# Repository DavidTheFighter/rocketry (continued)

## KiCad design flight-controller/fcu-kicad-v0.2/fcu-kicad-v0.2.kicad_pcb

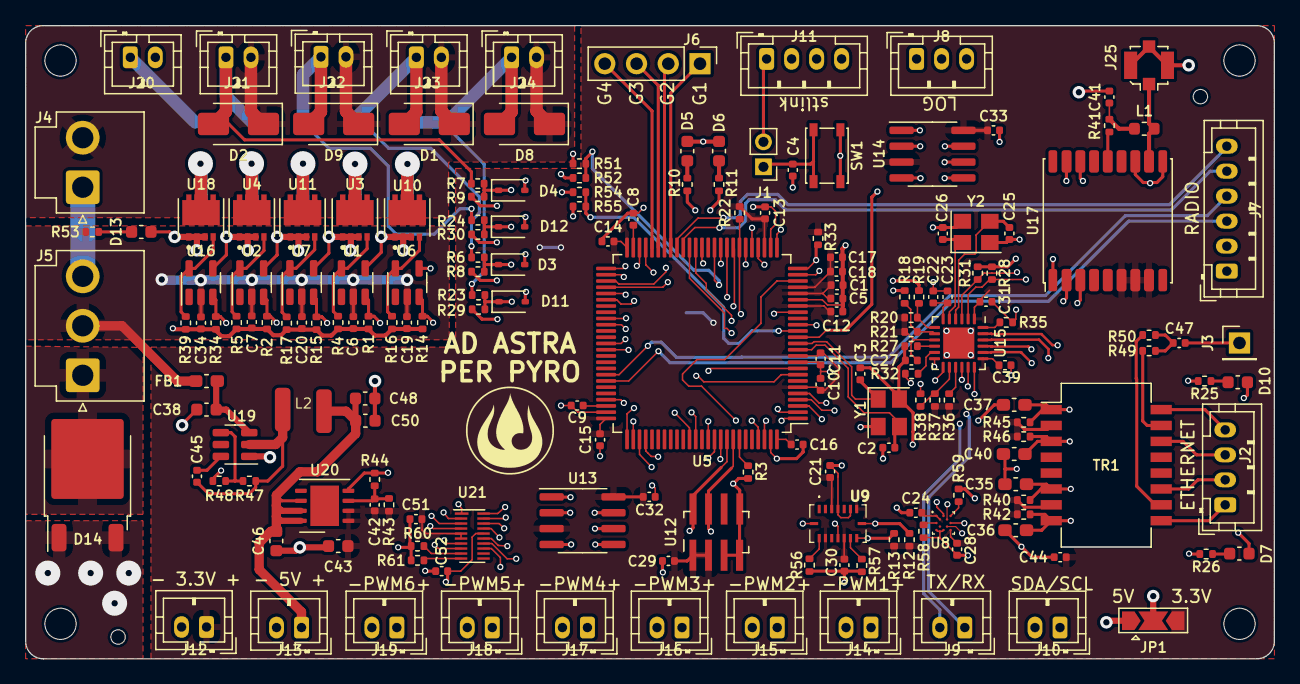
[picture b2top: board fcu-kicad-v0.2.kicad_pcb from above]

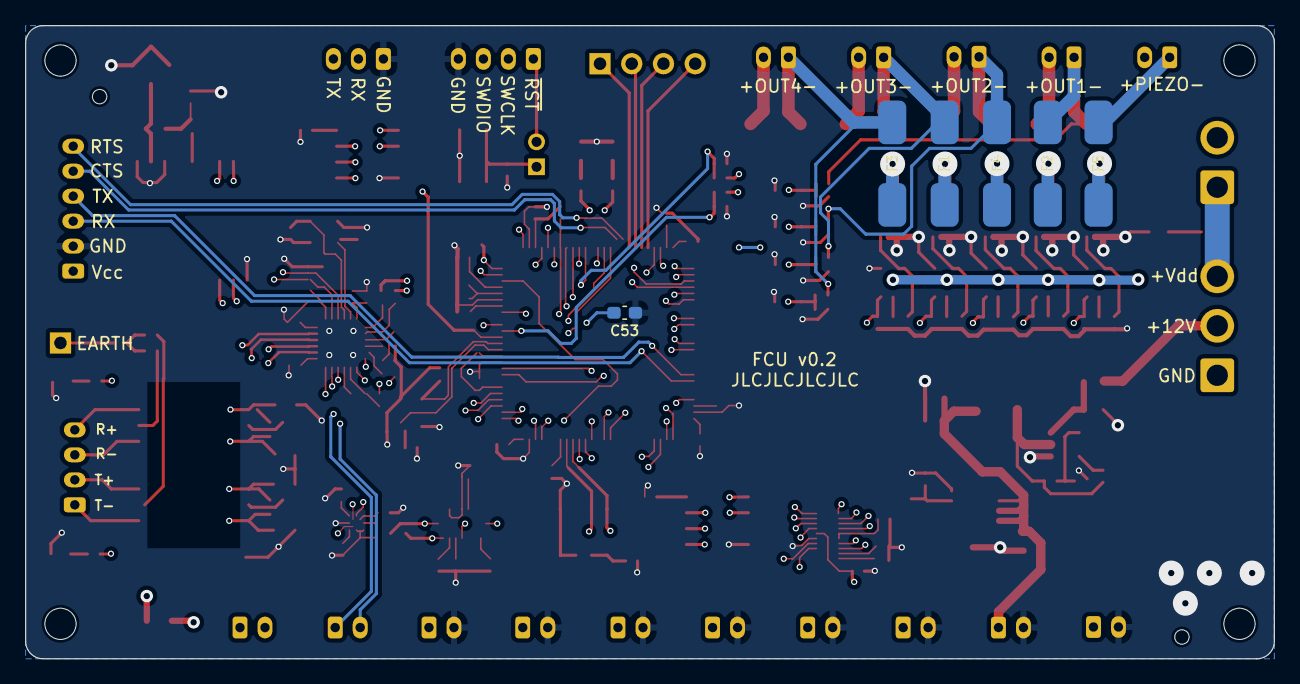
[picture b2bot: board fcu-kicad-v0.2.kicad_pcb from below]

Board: 4 copper layers, 99.9 x 50.7 mm, 186 parts (6 on the bottom side), 138 nets.

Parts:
C1, C6, C7, C17, C19, C20, C22, C34: 1uF; C_0402_1005Metric
C2, C3: 13pF; C_0402_1005Metric
C4, C5, C10, C11, C12, C13, C14, C15, C16, C18, C21, C24, C28, C29, C30, C32, C33, C45, C51, C52: 100nF; C_0402_1005Metric
C8, C9: 2.2uF; C_0402_1005Metric
C23: 470pF; C_0402_1005Metric
C25, C26: 15pF; C_0402_1005Metric
C27, C31, C39, C41: 10nF; C_0402_1005Metric
C35, C36, C37, C40: 10pF; C_0603_1608Metric_Pad1.08x0.95mm_HandSolder
C38, C43, C46: 10uF; C_0603_1608Metric
C42: 470nF; C_0402_1005Metric
C44: 22nF; C_0402_1005Metric
C47: 1nF; C_0402_1005Metric
C48, C50: 22uF; C_0603_1608Metric
C53: 4.7uF; C_0603_1608Metric_Pad1.08x0.95mm_HandSolder
D1, D2, D8, D9: GS1G; D_SMA
D3, D4, D11, D12: MM3Z3V0; D_SOD-323
D5: Blue; C_0603_1608Metric
D6: Red; C_0603_1608Metric
D7: Green; C_0603_1608Metric
D10: Yellow; C_0603_1608Metric
D13: Green_LED; C_0603_1608Metric
D14: MBRD20100; TO-252-2
F1, F2, F3, F4, F5: SF-2410F-T
FB1: FerriteBead; C_0603_1608Metric_Pad1.08x0.95mm_HandSolder
J1: Conn_01x02; PinHeader_1x02_P2.00mm_Vertical
J2, J11: Conn_01x04_Socket; JST_PH_B4B-PH-K_1x04_P2.00mm_Vertical
J3: Conn_01x01; PinHeader_1x01_P2.54mm_Vertical
J4: Conn_01x02_Socket; JST_VH_B2P-VH_1x02_P3.96mm_Vertical
J5: Conn_01x03_Pin; JST_VH_B3P-VH_1x03_P3.96mm_Vertical
J6: Conn_01x04_Socket; PinHeader_1x04_P2.54mm_Vertical
J7: Conn_01x06_Socket; JST_PH_B6B-PH-K_1x06_P2.00mm_Vertical
J8: Conn_01x03_Socket; JST_PH_B3B-PH-K_1x03_P2.00mm_Vertical
J9, J10, J12, J13, J14, J15, J16, J17, J18, J19, J20, J21, J22, J23, J24: Conn_01x02_Socket; JST_PH_B2B-PH-K_1x02_P2.00mm_Vertical
J25: Conn_01x02; U.FL_Molex_MCRF_73412-0110_Vertical
JP1: SolderJumper_3_Open; SolderJumper-3_P2.0mm_Open_TrianglePad1.0x1.5mm
L1: 27nH; L_0603_1608Metric
L2: 3.3uH; CKST353220
R1, R2, R4, R5, R14, R15, R16, R17, R34, R39, R54: 20K; R_0402_1005Metric
R3, R12, R13, R20, R21, R22, R27, R28, R31, R36, R37, R44, R48, R52, R56, R57, R58, R59, R60, R61: 10K; R_0402_1005Metric
R6, R7, R23, R24: 15K; R_0402_1005Metric
R8, R9, R29, R30, R53: 2.4K; R_0402_1005Metric
R10, R11, R25, R26: 220; R_0402_1005Metric
R18, R19, R32, R38: 33; R_0402_1005Metric
R33, R51, R55: 1.5K; R_0402_1005Metric
R35: 12.1K; R_0402_1005Metric
R40, R42, R45, R46: 49.9; R_0402_1005Metric
R41: 10; R_0402_1005Metric
R43, R47: 56.2K; R_0402_1005Metric
R49, R50: 75; R_0402_1005Metric
SW1: SW_RST; SW_SPST_PTS810
TR1: PT61017PEL; Transformer_Ethernet_Bourns_PT61017PEL
U1, U2, U6, U7, U16: MCP1416; SOT-23-5
U3, U4, U10, U11, U18: RQ3E100; HSMT-8
U5: STM32F407VGTx; LQFP-100_14x14mm_P0.5mm
U8: BMM150; WLCSP-12_1.56x1.56mm_P0.4mm
U9: BMI088
U12: MS5611-01BA; LGA-8_3x5mm_P1.25mm_HandSolder
U13, U14: W25X05; SOIC-8_3.9x4.9mm_P1.27mm
U15: LAN8742; VQFN-24-1EP_4x4mm_P0.5mm_EP2.5x2.5mm
U17: MAX-8C; ublox_MAX
U19: AP62300TWU; TSOT-23-6
U20: LD39200; DFN-8-1EP_4x4mm_P0.8mm_EP2.3x3.24mm
U21: TXB0108DQSR; USON-20_2x4mm_P0.4mm
Y1, Y2: 25 MHz; Crystal_SMD_3225-4Pin_3.2x2.5mm

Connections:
+3.3V: C1.1, C5.1, C10.2, C11.2, C12.2, C13.2, C14.2, C15.2, C16.2, C17.2, C18.2, C21.1, C24.2, C27.2, C28.1, C29.1, C30.1, C31.1, C32.2, C33.2, C39.1, C42.2, C43.2, C44.1, C51.2, C53.2, J12.1, JP1.3 (B), R12.2, R13.2, R20.2, R21.2, R22.2, R33.1, R36.2, R37.2, R40.1, R42.1, R43.1, R45.1, R46.1, TR1.2 (C_TD), TR1.7 (C_RD), U5.6 (VBAT), U5.11 (VDD), U5.19 (VDD), U5.21 (VREF+), U5.22 (VDDA), U5.28 (VDD), U5.50 (VDD), U5.75 (VDD), U5.100 (VDD), U8.A1 (PS), U8.B2 (VDDIO), U8.E5 (VDD), U9.3 (VDD), U9.7 (PS), U9.11 (VDDIO), U9.14 (CSB1), U12.1 (VDD), U12.2 (PS), U13.3 (WP), U13.8 (VCC), U14.3 (WP), U14.8 (VCC), U15.1 (VDD2A), U15.9 (VDDIO), U15.19 (VDD1A), U17.6 (V_BCKP), U17.7 (VCC_IO), U17.8 (VCC), U20.1 (OUT), U20.2 (OUT), U21.5 (VCCA), U21.6 (OE)
+5V: C46.2, C48.1, C50.1, C52.2, J13.1, JP1.1 (A), L2.2, U20.6 (EN), U20.7 (IN), U20.8 (IN), U21.16 (VCCB)
+12V: C6.2, C7.2, C19.2, C20.2, C34.2, FB1.1, J5.2, J20.2, R52.1, R53.2, U1.2 (Vdd), U2.2 (Vdd), U6.2 (Vdd), U7.2 (Vdd), U16.2 (Vdd)
/DRX+: C40.1, R46.2, TR1.3 (TD-), U15.23 (RXP)
/DRX-: C37.1, R45.2, TR1.1 (TD+), U15.22 (RXN)
/DTX+: C36.1, R42.2, TR1.8 (RD-), U15.21 (TXP)
/DTX-: C35.1, R40.2, TR1.6 (RD+), U15.20 (TXN)
/RX+: J2.4, TR1.16 (TX+)
/RX-: J2.3, TR1.14 (TX-)
/TX+: J2.2, TR1.11 (RX+)
/TX-: J2.1, TR1.9 (RX-)
ACCEL_INT: U5.39 (PE8), U9.16 (INT1)
ADC1_IN3: D4.1 (K), R7.2, R9.1, U5.26 (PA3)
ADC1_IN4: D12.1 (K), R24.2, R30.1, U5.29 (PA4)
ADC1_IN6: D3.1 (K), R6.2, R8.1, U5.31 (PA6)
ADC1_IN8: D11.1 (K), R23.2, R29.1, U5.35 (PB0)
ADC1_IN9: R51.1, R52.2, U5.36 (PB1)
ADC1_IN10: R54.2, R55.1, U5.15 (PC0)
BLDR_FLASH_CSN: U5.5 (PE6), U14.1 (CS)
BLDR_FLASH_HOLD: U5.38 (PE7), U14.7 (HOLD)
BMM150_INT: U5.18 (PC3), U8.D4 (DRDY)
ETH_CRS_DV: R22.1, R32.1, U5.32 (PA7)
ETH_MDC: U5.16 (PC1), U15.13 (MDC)
ETH_MDIO: R33.2, U5.25 (PA2), U15.12 (MDIO)
ETH_REF_CLK: R38.2, U5.24 (PA1)
ETH_RXD0: R18.2, U5.33 (PC4)
ETH_RXD1: R19.1, U5.34 (PC5)
ETH_TXD0: U5.51 (PB12), U15.17 (TDX0)
ETH_TXD1: U5.52 (PB13), U15.18 (TXD1)
ETH_TX_EN: U5.48 (PB11), U15.16 (TXEN)
Earth: C47.2, J3.1
GND: C1.2, C2.1, C3.1, C4.2, C5.2, C6.1, C7.1, C8.1, C9.1, C10.1, C11.1, C12.1, C13.1, C14.1, C15.1, C16.1, C17.1, C18.1, C19.1, C20.1, C21.2, C22.1, C23.1, C24.1, C25.1, C26.1, C27.1, C28.2, C29.2, C30.2, C31.2, C32.1, C33.1, C34.1, C35.2, C36.2, C37.2, C38.1, C39.2, C40.2, C41.2, C43.1, C44.2, C46.1, C48.2, C50.2, C51.1, C52.1, C53.1, D3.2 (A), D4.2 (A), D5.1 (K), D6.1 (K), D7.1 (K), D10.1 (K), D11.2 (A), D12.2 (A), D13.1 (K), D14.2 (A), J7.2, J8.1, J11.4, J12.2, J13.2, J14.2, J15.2, J16.2, J17.2, J18.2, J19.2, J25.2, R1.1, R2.1, R3.1, R4.2, R5.2, R8.2, R9.2, R14.1, R15.1, R16.2, R17.2, R27.1, R28.2, R29.2, R30.2, R31.2, R34.1, R35.2, R39.2, R44.2, R48.2, R51.2, R55.2, R56.2, R57.2, R58.1, R59.1, R60.2, R61.1, SW1.2 (B), U1.4 (GND), U2.4 (GND), U3.1 (Source), U3.2 (Source), U3.3 (Source), U4.1 (Source), U4.2 (Source), U4.3 (Source), U5.10 (VSS), U5.20 (VSSA), U5.27 (VSS), U5.74 (VSS), U5.99 (VSS), U6.4 (GND), U7.4 (GND), U8.C5 (GND), U8.E1 (GND), U8.E3 (GND), U9.4 (GNDA), U9.6 (GNDIO), U10.1 (Source), U10.2 (Source), U10.3 (Source), U11.1 (Source), U11.2 (Source), U11.3 (Source), U12.3 (GND), U12.4 (CSB), U12.5 (CSB), U13.4 (GND), U14.4 (GND), U15.25 (VSS), U16.4 (GND), U17.1 (GND), U17.10 (GND), U17.12 (GND), U18.1 (Source), U18.2 (Source), U18.3 (Source), U19.1 (GND), U20.4 (GND), U21.15 (GND), Y1.2, Y1.4, Y2.2, Y2.4
GPIO1: J6.1, U5.43 (PE12)
GPIO2: J6.2, U5.44 (PE13)
GPIO3: J6.3, U5.45 (PE14)
GPIO4: J6.4, U5.46 (PE15)
GYRO_INT: U5.40 (PE9), U9.12 (INT3)
I2C1_SCL: J10.1, R12.1, U5.92 (PB6), U8.A3 (SCK), U9.8 (SCL/SCK), U12.8 (SCLK), U17.17 (SCL)
I2C1_SDA: J10.2, R13.1, U5.93 (PB7), U8.B4 (SDI), U9.9 (SDA/SDI), U12.7 (SDI/SDA), U17.16 (SDA)
LOG_FLASH_CSN: U5.3 (PE4), U13.1 (CS)
LOG_FLASH_HOLD: U5.4 (PE5), U13.7 (HOLD)
unnamed: C41.1, L1.1, R41.2
unnamed: C47.1, R49.2, R50.2
unnamed: D5.2 (A), R10.1
unnamed: D6.2 (A), R11.1
unnamed: D7.2 (A), R26.1
unnamed: D10.2 (A), R25.1
unnamed: D13.2 (A), R53.1
unnamed: D14.1 (K), J5.1
unnamed: F1.1, U3.5 (Drain)
unnamed: F2.1, U4.5 (Drain)
unnamed: F3.1, U10.5 (Drain)
unnamed: F4.1, U11.5 (Drain)
unnamed: F5.1, U18.5 (Drain)
unnamed: C4.1, J1.1, SW1.1 (A)
unnamed: J4.1, J5.3, R54.1
unnamed: J7.1, JP1.2 (C)
unnamed: J14.1, U21.20 (B1)
unnamed: J15.1, U21.19 (B2)
unnamed: J16.1, U21.18 (B3)
unnamed: J17.1, U21.17 (B4)
unnamed: J18.1, U21.14 (B5)
unnamed: J19.1, U21.13 (B6)
unnamed: R50.1, TR1.10 (C_RX)
unnamed: R49.1, TR1.15 (C_TX)
unnamed: R4.1, U1.5 (OUT), U3.4 (Gate)
unnamed: R5.1, U2.5 (OUT), U4.4 (Gate)
unnamed: R3.2, U5.94 (BOOT0)
unnamed: R10.2, U5.8 (PC14)
unnamed: R11.2, U5.9 (PC15)
unnamed: C2.2, U5.12 (PH0), Y1.3
unnamed: C3.2, U5.13 (PH1), Y1.1
unnamed: C8.2, U5.49 (VCAP_1)
unnamed: C9.2, U5.73 (VCAP_2)
unnamed: R59.2, U8.A5 (CSB)
unnamed: R58.2, U8.C1 (SDO)
unnamed: R56.1, U9.15 (SDO1)
unnamed: R57.1, U9.10 (SDO2)
unnamed: R16.1, U6.5 (OUT), U10.4 (Gate)
unnamed: R17.1, U7.5 (OUT), U11.4 (Gate)
unnamed: R32.2, U15.11 (CRS_DV)
unnamed: R26.2, R31.1, U15.3 (LED1)
unnamed: R25.2, R28.1, U15.2 (LED2)
unnamed: R35.1, U15.24 (RBIAS)
unnamed: R18.1, R21.1, U15.8 (RXD0)
unnamed: R19.2, R20.1, U15.7 (RXD1)
unnamed: R27.2, U15.10 (RXER)
unnamed: C22.2, C23.2, U15.6 (VDDCR)
unnamed: C25.2, U15.4 (XTAL2), Y2.3
unnamed: C26.2, U15.5 (XTAl1), Y2.1
unnamed: R37.1, R38.1, U15.14 (~INT)
unnamed: R36.1, U15.15 (~RST)
unnamed: R39.1, U16.5 (OUT), U18.4 (Gate)
unnamed: R41.1, U17.14 (VCC_RF)
unnamed: C45.2, U19.6 (BST)
unnamed: R47.2, R48.1, U19.4 (FB)
unnamed: C38.2, FB1.2, U19.3 (IN)
unnamed: C45.1, L2.1, R47.1, U19.2 (SW)
unnamed: C42.1, R43.2, R44.1, U20.3 (ADJ)
unnamed: R60.1, U21.9 (A7)
unnamed: R61.2, U21.10 (A8)
OUT1: D2.2 (A), F2.2, J21.1, R7.1
OUT1_CTRL: R2.2, U2.3 (IN), U5.97 (PE0)
OUT2: D9.2 (A), F4.2, J22.1, R24.1
OUT2_CTRL: R15.2, U5.98 (PE1), U7.3 (IN)
OUT3: D1.2 (A), F1.2, J23.1, R6.1
OUT3_CTRL: R1.2, U1.3 (IN), U5.1 (PE2)
OUT4: D8.2 (A), F3.2, J24.1, R23.1
OUT4_CTRL: R14.2, U5.2 (PE3), U6.3 (IN)
PIEZO: F5.2, J20.1
RADIO_CTS: J7.5, U5.41 (PE10)
RADIO_RTS: J7.6, U5.42 (PE11)
RF_IN: J25.1, L1.2, U17.11 (RF_IN)
SPI1_MISO: U5.90 (PB4), U13.2 (DO)
SPI1_MOSI: U5.91 (PB5), U13.5 (DI)
SPI1_SCK: U5.30 (PA5), U13.6 (CLK)
SPI2_MISO: U5.53 (PB14), U14.2 (DO)
SPI2_MOSI: U5.54 (PB15), U14.5 (DI)
SPI2_SCK: U5.47 (PB10), U14.6 (CLK)
SWCLK: J11.2, U5.76 (PA14)
SWDIO: J11.3, U5.72 (PA13)
TIM2_CH1: U5.77 (PA15), U21.1 (A1)
TIM2_CH2: U5.89 (PB3), U21.2 (A2)
TIM3_CH1: U5.63 (PC6), U21.3 (A3)
TIM3_CH2: U5.64 (PC7), U21.4 (A4)
TIM4_CH1: U5.59 (PD12), U21.7 (A5)
TIM4_CH2: U5.60 (PD13), U21.8 (A6)
TIM5_CH1: R34.2, U5.23 (PA0), U16.3 (IN)
UART4_RX: U5.79 (PC11), U17.2 (TXD)
UART4_TX: U5.78 (PC10), U17.3 (RXD)
USART1_RX: J7.3, U5.69 (PA10)
USART1_TX: J7.4, U5.68 (PA9)
USART2_RX: J8.2, U5.87 (PD6)
USART2_TX: J8.3, U5.86 (PD5)
USART3_RX: J9.1, U5.56 (PD9)
USART3_TX: J9.2, U5.55 (PD8)
Vdrive: D1.1 (K), D2.1 (K), D8.1 (K), D9.1 (K), J4.2, J21.2, J22.2, J23.2, J24.2
~MCU_RST: J1.2, J11.1, U5.14 (NRST)

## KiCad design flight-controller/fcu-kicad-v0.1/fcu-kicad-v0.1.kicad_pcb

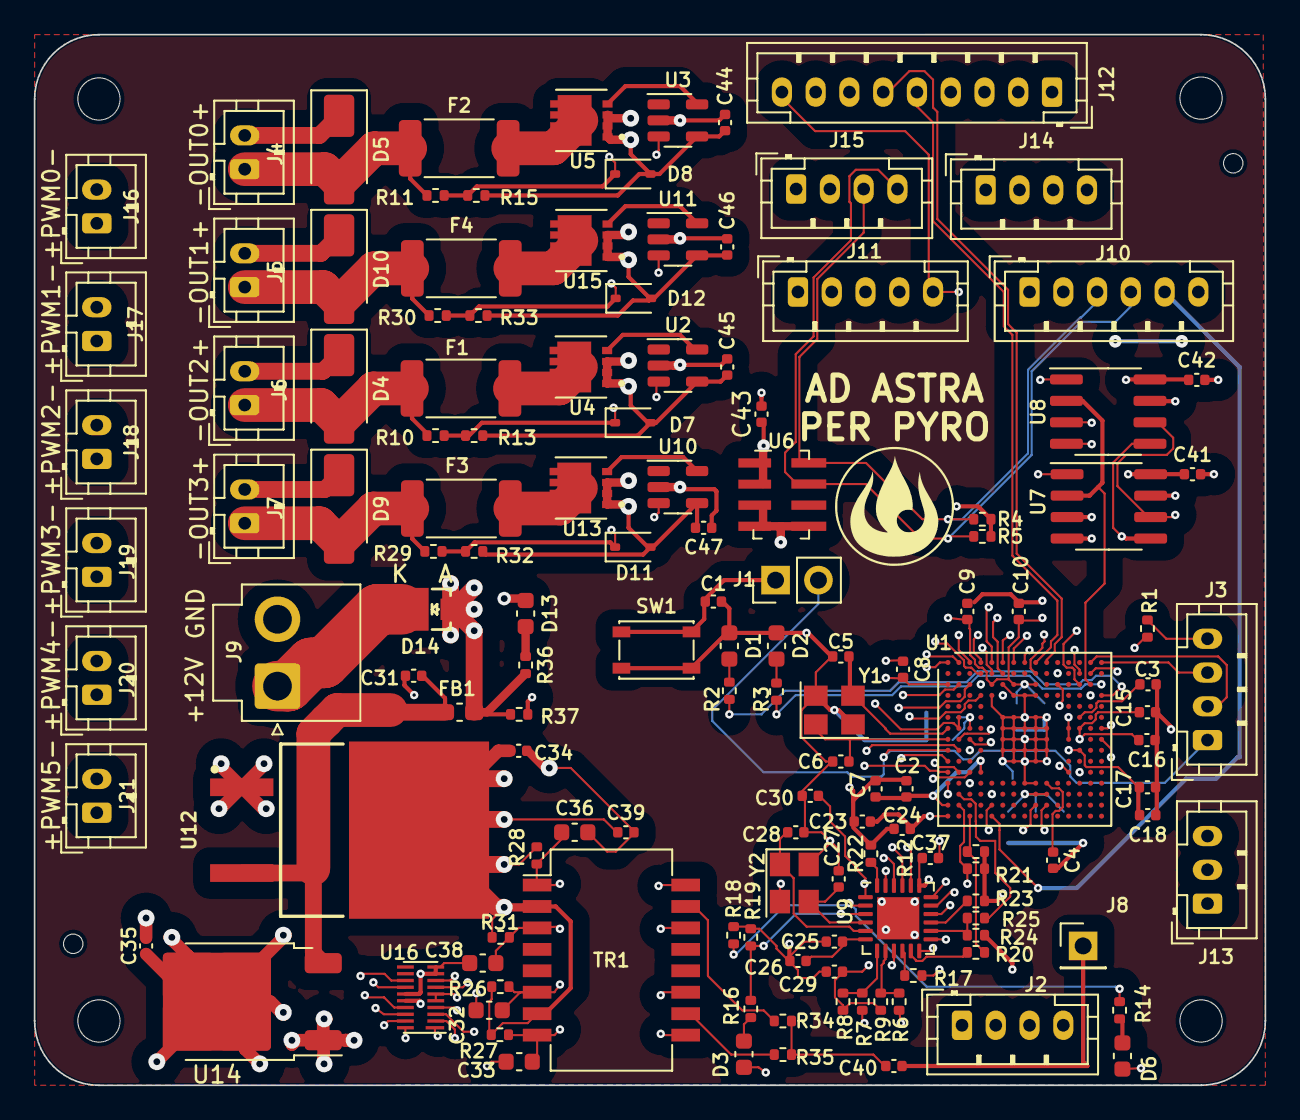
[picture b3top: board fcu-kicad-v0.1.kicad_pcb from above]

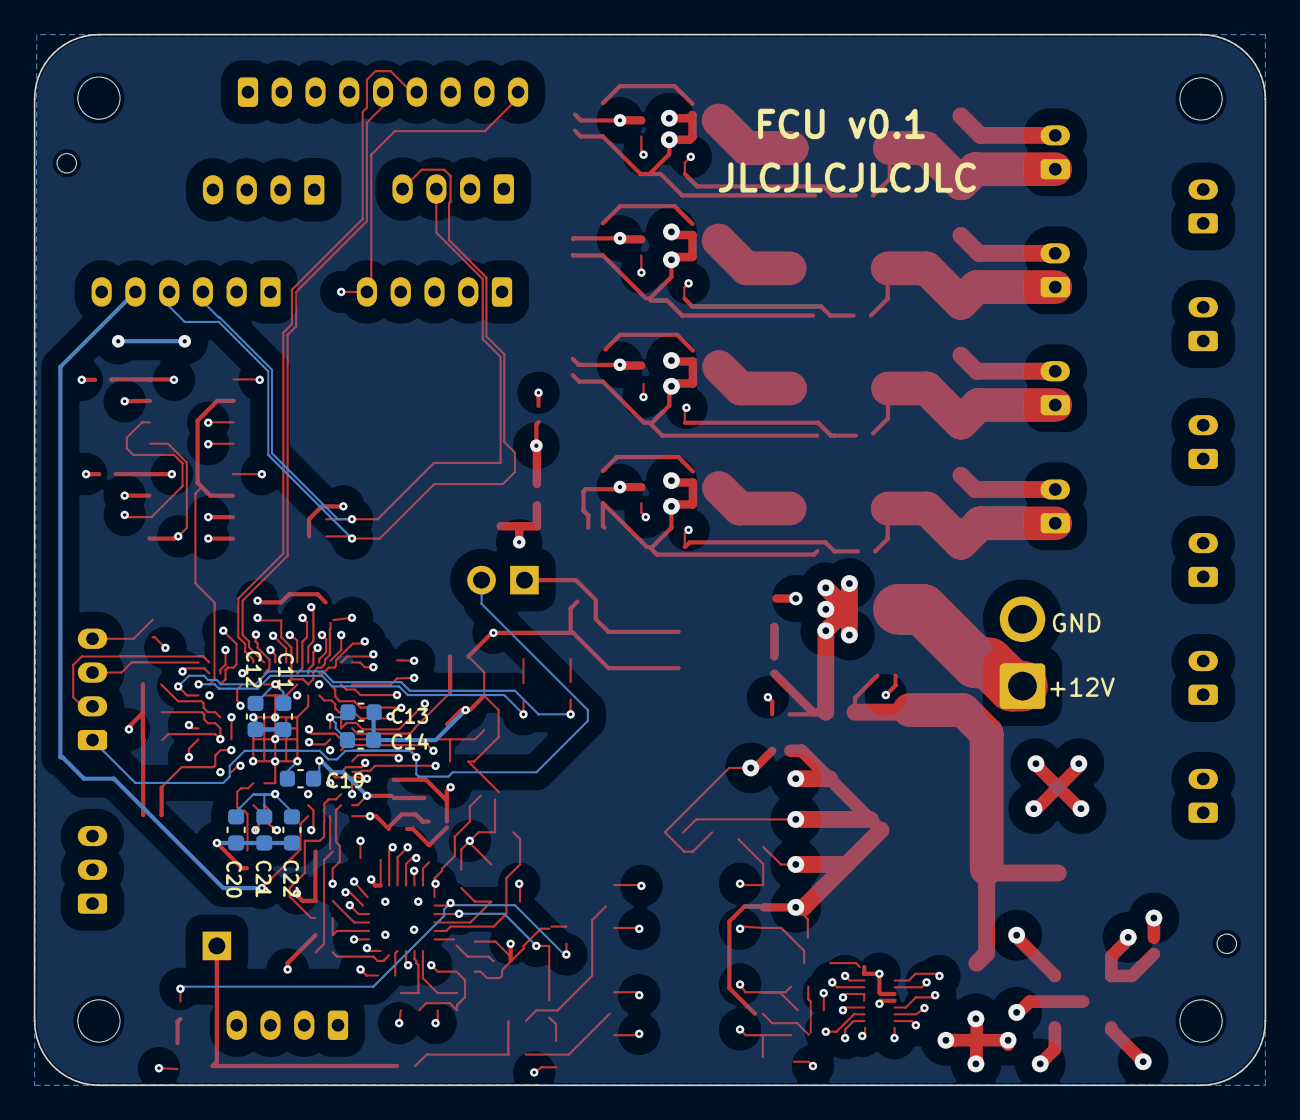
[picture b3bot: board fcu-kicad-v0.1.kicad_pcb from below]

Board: 4 copper layers, 72.9 x 62.2 mm, 144 parts (8 on the bottom side), 110 nets.

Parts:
C1, C7, C8, C9, C10, C15, C16, C17, C18, C24, C41, C42, C43: 100nF; C_0402_1005Metric
C2, C23, C25, C44, C45, C46, C47: 1uF; C_0402_1005Metric
C3, C4: 2.2uF; C_0402_1005Metric
C5, C6: 13pF; C_0402_1005Metric
C11, C12, C13, C14, C19, C20, C21, C22: 100nF; C_0603_1608Metric
C26: 470pF; C_0402_1005Metric
C27, C28: 15pF; C_0402_1005Metric
C29, C30, C37: 10nF; C_0402_1005Metric
C31, C34, C35: 10uF; C_0402_1005Metric
C32, C33, C36, C38: 10pF DNP; C_0603_1608Metric
C39: 22nF; C_0402_1005Metric
C40: 1nF; C_0402_1005Metric
D1: Blue; C_0603_1608Metric
D2: Red; C_0603_1608Metric
D3: Green; C_0603_1608Metric
D4, D5, D9, D10: GS1G; D_SMA
D6: Yellow; C_0603_1608Metric
D7, D8, D11, D12: MM3Z3V0; D_SOD-323
D13: Green_LED; C_0603_1608Metric
D14: SS1P3L-M3/84A; D0-220AA-SMP
F1, F2, F3, F4: SF-2410F-T; Fuse_2512_6332Metric
FB1: FerriteBead; C_0603_1608Metric_Pad1.08x0.95mm_HandSolder
J1: Conn_01x02; PinHeader_1x02_P2.54mm_Vertical
J2, J3, J14, J15: Conn_01x04_Socket; JST_PH_B4B-PH-K_1x04_P2.00mm_Vertical
J4, J5, J6, J7, J16, J17, J18, J19, J20, J21: Conn_01x02_Socket; JST_PH_B2B-PH-K_1x02_P2.00mm_Vertical
J8: Conn_01x01; PinHeader_1x01_P2.54mm_Vertical
J9: Conn_01x02_Pin; JST_VH_B2P-VH_1x02_P3.96mm_Vertical
J10: Conn_01x06_Socket; JST_PH_B6B-PH-K_1x06_P2.00mm_Vertical
J11: Conn_01x05_Socket; JST_PH_B5B-PH-K_1x05_P2.00mm_Vertical
J12: Conn_01x09_Socket; JST_PH_B9B-PH-K_1x09_P2.00mm_Vertical
J13: Conn_01x03_Socket; JST_PH_B3B-PH-K_1x03_P2.00mm_Vertical
R1, R4, R5, R8, R9, R12, R17, R18, R19, R23, R24, R37: 10K; R_0402_1005Metric
R2, R3: 220; R_0402_1005Metric
R6, R7, R20, R25: 33; R_0402_1005Metric
R10, R11, R29, R30: 12K; R_0402_1005Metric
R13, R15, R32, R33: 2.4K; R_0402_1005Metric
R14, R16: 250; R_0402_1005Metric
R21: 1.5K; R_0402_1005Metric
R22: 12.1K; R_0402_1005Metric
R26, R27, R28, R31: 49.9; R_0402_1005Metric
R34, R35: 75; R_0402_1005Metric
R36: 1K; R_0402_1005Metric
SW1: SW_RST; SW_SPST_PTS810
TR1: PT61017PEL; Transformer_Ethernet_Bourns_PT61017PEL
U1: STM32F407IGHx; UFBGA-201_10x10mm_Layout15x15_P0.65mm
U2, U3, U10, U11: MCP1416; SOT-23-5
U4, U5, U13, U15: RQ3E100; HSMT-8
U6: MS5611-01BA; LGA-8_3x5mm_P1.25mm
U7, U8: W25X05; SOIC-8_3.9x4.9mm_P1.27mm
U9: LAN8742; VQFN-24-1EP_4x4mm_P0.5mm_EP2.5x2.5mm
U12: LD1085D2T33R; TO254P1542X460-3N
U14: NCP1117-5.0_SOT223; TO-252-2
U16: TXB0108DQSR; USON-20_2x4mm_P0.4mm
Y1, Y2: 25 MHz; Crystal_SMD_3225-4Pin_3.2x2.5mm

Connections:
+3.3V: C2.1, C7.1, C8.2, C9.2, C10.2, C11.2, C12.2, C13.2, C14.2, C15.2, C16.2, C17.2, C18.2, C19.2, C20.2, C21.2, C22.2, C23.2, C24.2, C29.2, C30.1, C34.1, C37.1, C39.1, C41.1, C42.1, C43.1, J10.1, J11.1, J12.1, J14.1, J15.1, R4.2, R5.2, R8.2, R9.2, R12.2, R21.1, R23.2, R24.2, R26.1, R27.1, R28.1, R31.1, TR1.2 (C_TD), TR1.7 (C_RD), U1.C1 (VBAT), U1.C5 (VDD), U1.C7 (VDD), U1.C8 (VDD), U1.C9 (VDD), U1.F3 (VDD), U1.G3 (VDD), U1.G13 (VDD), U1.H13 (VDD), U1.J12 (VDD), U1.J13 (VDD), U1.K4 (VDD), U1.L4 (BYPASS_REG), U1.N8 (VDD), U1.N9 (VDD), U1.N10 (VDD), U1.P1 (VREF+), U1.R1 (VDDA), U6.1 (VDD), U6.2 (PS), U7.3 (WP), U7.8 (VCC), U8.3 (WP), U8.8 (VCC), U9.1 (VDD2A), U9.9 (VDDIO), U9.19 (VDD1A), U12.4 (VO), U16.5 (VCCA), U16.6 (OE)
+5V: C35.1, U14.2 (VO), U16.16 (VCCB)
+12V: C44.2, C45.2, C46.2, C47.2, D4.1 (K), D5.1 (K), D9.1 (K), D10.1 (K), D14.1 (K), FB1.1, J4.2, J5.2, J6.2, J7.2, R36.2, R37.1, U2.2 (Vdd), U3.2 (Vdd), U10.2 (Vdd), U11.2 (Vdd)
/DRX+: C38.1, R31.2, TR1.3 (TD-), U9.23 (RXP)
/DRX-: C36.1, R28.2, TR1.1 (TD+), U9.22 (RXN)
/DTX+: C33.1, R27.2, TR1.8 (RD-), U9.21 (TXP)
/DTX-: C32.1, R26.2, TR1.6 (RD+), U9.20 (TXN)
/RX+: J2.4, TR1.16 (TX+)
/RX-: J2.3, TR1.14 (TX-)
/TX+: J2.2, TR1.11 (RX+)
/TX-: J2.1, TR1.9 (RX-)
ADC3_IN5: D8.1 (K), R11.2, R15.1, U1.K1 (PF7)
ADC3_IN6: D12.1 (K), R30.2, R33.1, U1.L3 (PF8)
ADC3_IN7: D7.1 (K), R10.2, R13.1, U1.L2 (PF9)
ADC3_IN8: D11.1 (K), R29.2, R32.1, U1.L1 (PF10)
BLDR_FLASH_CSN: U1.C3 (PI6), U8.1 (CS)
BLDR_FLASH_HOLD: U1.C2 (PI7), U8.7 (HOLD)
ETH_CRS_DV: R12.1, R20.1, U1.R3 (PA7)
ETH_MDC: U1.M3 (PC1), U9.13 (MDC)
ETH_MDIO: R21.2, U1.P2 (PA2), U9.12 (MDIO)
ETH_REF_CLK: R25.2, U1.N2 (PA1)
ETH_RXD0: R6.2, U1.N5 (PC4)
ETH_RXD1: R7.1, U1.P5 (PC5)
ETH_TXD0: U1.A8 (PG13), U9.17 (TDX0)
ETH_TXD1: U1.A7 (PG14), U9.18 (TXD1)
ETH_TX_EN: U1.B9 (PG11), U9.16 (TXEN)
Earth: C40.2, J8.1
GND: C1.2, C2.2, C3.1, C4.1, C5.1, C6.1, C7.2, C8.1, C9.1, C10.1, C11.1, C12.1, C13.1, C14.1, C15.1, C16.1, C17.1, C18.1, C19.1, C20.1, C21.1, C22.1, C23.1, C24.1, C25.1, C26.1, C27.1, C28.1, C29.1, C30.2, C31.1, C32.2, C33.2, C34.2, C35.2, C36.2, C37.2, C38.2, C39.2, C41.2, C42.2, C43.2, C44.1, C45.1, C46.1, C47.1, D1.1 (K), D2.1 (K), D3.1 (K), D6.1 (K), D7.2 (A), D8.2 (A), D11.2 (A), D12.2 (A), D13.1 (K), J3.4, J9.2, J10.2, J11.2, J12.2, J13.1, J14.2, J15.2, J16.2, J17.2, J18.2, J19.2, J20.2, J21.2, R1.1, R13.2, R15.2, R17.1, R18.2, R19.2, R22.2, R32.2, R33.2, R37.2, SW1.2 (B), U1.C6 (PDR_ON), U1.D5 (VSS), U1.D7 (VSS), U1.D8 (VSS), U1.D9 (VSS), U1.F2 (VSS), U1.F6 (VSS), U1.F7 (VSS), U1.F8 (VSS), U1.F9 (VSS), U1.F10 (VSS), U1.F12 (VSS), U1.G2 (VSS), U1.G6 (VSS), U1.G7 (VSS), U1.G8 (VSS), U1.G9 (VSS), U1.G10 (VSS), U1.G12 (VSS), U1.H6 (VSS), U1.H7 (VSS), U1.H8 (VSS), U1.H9 (VSS), U1.H10 (VSS), U1.H12 (VSS), U1.J6 (VSS), U1.J7 (VSS), U1.J8 (VSS), U1.J9 (VSS), U1.J10 (VSS), U1.K6 (VSS), U1.K7 (VSS), U1.K8 (VSS), U1.K9 (VSS), U1.K10 (VSS), U1.M1 (VSSA), U1.M8 (VSS), U1.M9 (VSS), U1.N1 (VREF-), U2.4 (GND), U3.4 (GND), U4.1 (Source), U4.2 (Source), U4.3 (Source), U5.1 (Source), U5.2 (Source), U5.3 (Source), U6.3 (GND), U6.4 (CSB), U6.5 (CSB), U7.4 (GND), U8.4 (GND), U9.25 (VSS), U10.4 (GND), U11.4 (GND), U12.1 (GND), U13.1 (Source), U13.2 (Source), U13.3 (Source), U14.1 (GND), U15.1 (Source), U15.2 (Source), U15.3 (Source), U16.9 (A7), U16.10 (A8), U16.15 (GND), Y1.2, Y1.4, Y2.2, Y2.4
I2C1_SCL: J10.3, J15.3, R4.1, U1.A5 (PB8), U6.8 (SCLK)
I2C1_SDA: J10.4, J15.4, R5.1, U1.B4 (PB9), U6.7 (SDI/SDA)
IMU_IRQ: J10.6, U1.A1 (PE3)
LOG_FLASH_CSN: U1.D4 (PI4), U7.1 (CS)
LOG_FLASH_HOLD: U1.C4 (PI5), U7.7 (HOLD)
unnamed: C40.1, R34.2, R35.2
unnamed: D1.2 (A), R2.1
unnamed: D2.2 (A), R3.1
unnamed: D3.2 (A), R16.1
unnamed: D6.2 (A), R14.1
unnamed: D13.2 (A), R36.1
unnamed: D14.2 (A), J9.1
unnamed: F1.1, U4.5 (Drain)
unnamed: F2.1, U5.5 (Drain)
unnamed: F3.1, U13.5 (Drain)
unnamed: F4.1, U15.5 (Drain)
unnamed: C1.1, J1.1, SW1.1 (A)
unnamed: J16.1, U16.20 (B1)
unnamed: J17.1, U16.19 (B2)
unnamed: J18.1, U16.18 (B3)
unnamed: J19.1, U16.17 (B4)
unnamed: J20.1, U16.14 (B5)
unnamed: J21.1, U16.13 (B6)
unnamed: R35.1, TR1.10 (C_RX)
unnamed: R34.1, TR1.15 (C_TX)
unnamed: R1.2, U1.D6 (BOOT0)
unnamed: R2.2, U1.D15 (PA10)
unnamed: R3.2, U1.C15 (PA11)
unnamed: C5.2, U1.G1 (PH0), Y1.3
unnamed: C6.2, U1.H1, Y1.1
unnamed: C4.2, U1.M10 (VCAP_1)
unnamed: C3.2, U1.F13 (VCAP_2)
unnamed: U2.5 (OUT), U4.4 (Gate)
unnamed: U3.5 (OUT), U5.4 (Gate)
unnamed: R20.2, U9.11 (CRS_DV)
unnamed: R16.2, R19.1, U9.3 (LED1)
unnamed: R14.2, R18.1, U9.2 (LED2)
unnamed: R22.1, U9.24 (RBIAS)
unnamed: R6.1, R9.1, U9.8 (RXD0)
unnamed: R7.2, R8.1, U9.7 (RXD1)
unnamed: R17.2, U9.10 (RXER)
unnamed: C25.2, C26.2, U9.6 (VDDCR)
unnamed: C27.2, U9.4 (XTAL2), Y2.3
unnamed: C28.2, U9.5 (XTAl1), Y2.1
unnamed: R24.1, R25.1, U9.14 (~INT)
unnamed: R23.1, U9.15 (~RST)
unnamed: U10.5 (OUT), U13.4 (Gate)
unnamed: U11.5 (OUT), U15.4 (Gate)
unnamed: C31.2, FB1.2, U12.3 (VI), U14.3 (VI)
RADIO_CE: J12.8, U1.A2 (PE2)
RADIO_IRQ: J12.7, U1.A3 (PE1)
SPI1_MISO: J12.5, U1.A9 (PB4)
SPI1_MOSI: J12.4, U1.A6 (PB5)
SPI1_SCK: J12.6, U1.A10 (PB3)
SPI2_MISO: U1.C14 (PI2), U7.2 (DO), U8.2 (DO)
SPI2_MOSI: U1.C13 (PI3), U7.5 (DI), U8.5 (DI)
SPI2_SCK: U1.D14 (PI1), U7.6 (CLK), U8.6 (CLK)
SWCLK: J3.2, U1.A14
SWDIO: J3.3, U1.A15 (PA13)
SWT1: D5.2 (A), F2.2, J4.1, R11.1
SWT1_CTRL: U1.H3 (PF1), U3.3 (IN)
SWT2: D10.2 (A), F4.2, J5.1, R30.1
SWT2_CTRL: U1.H2 (PF2), U11.3 (IN)
SWT3: D4.2 (A), F1.2, J6.1, R10.1
SWT3_CTRL: U1.J2 (PF3), U2.3 (IN)
SWT4: D9.2 (A), F3.2, J7.1, R29.1
SWT4_CTRL: U1.J3 (PF4), U10.3 (IN)
TIM1_CH1: U1.P9 (PE9), U16.1 (A1)
TIM1_CH2: U1.P10 (PE11), U16.2 (A2)
TIM3_CH1: U1.H15 (PC6), U16.3 (A3)
TIM3_CH2: U1.G15 (PC7), U16.4 (A4)
TIM5_CH1: U1.L13 (PH10), U16.7 (A5)
TIM5_CH2: U1.L12 (PH11), U16.8 (A6)
USART1_RX: J11.3, U1.B5 (PB7)
USART1_TX: J11.4, U1.B6
USART2_RX: J13.2, U1.B11 (PD6)
USART2_TX: J13.3, U1.C11 (PD5)
USART3_RX: J14.3, U1.B13 (PC11)
USART3_TX: J14.4, U1.B14 (PC10)
~CSN_RADIO: J12.3, U1.A4 (PE0)
~MCU_RST: J1.2, J3.1, U1.J1 (NRST)
~RST: J10.5, J11.5, J12.9, U1.R5 (PB0)

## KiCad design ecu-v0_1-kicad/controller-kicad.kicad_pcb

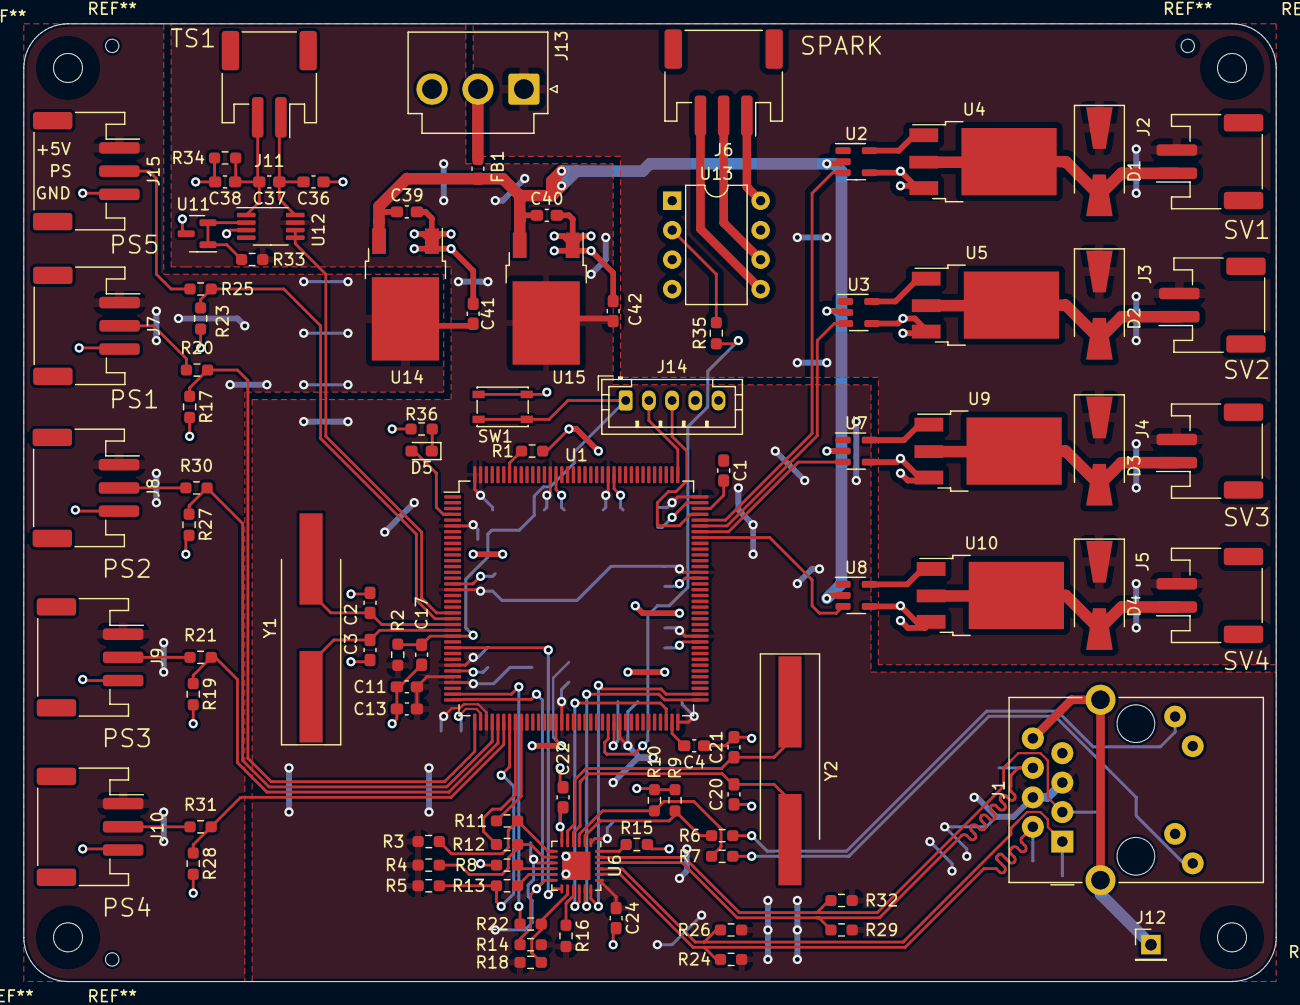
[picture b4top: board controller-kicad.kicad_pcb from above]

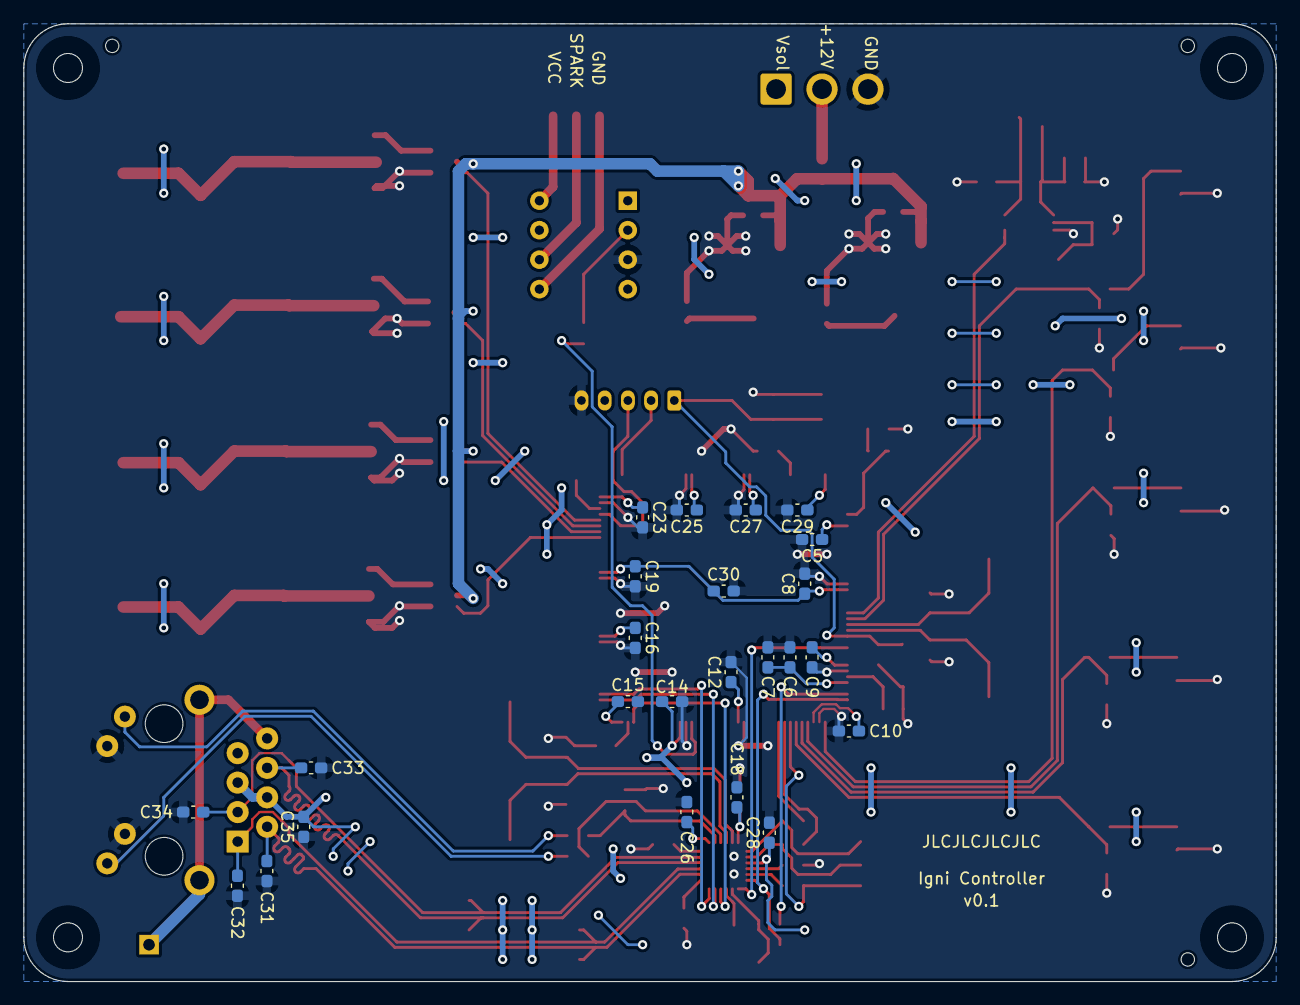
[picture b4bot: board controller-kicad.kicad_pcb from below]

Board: 2 copper layers, 108.0 x 82.5 mm, 117 parts (24 on the bottom side), 75 nets.

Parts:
C1, C4: 2.2uF; C_0603_1608Metric_Pad1.08x0.95mm_HandSolder
C2, C3: 23pF; C_0603_1608Metric_Pad1.08x0.95mm_HandSolder
C5, C6, C8, C9, C10, C11, C12, C14, C15, C16, C17, C19, C23, C25, C27, C29, C37: 100nF; C_0603_1608Metric_Pad1.08x0.95mm_HandSolder
C7, C13, C18: 1uF; C_0603_1608Metric_Pad1.08x0.95mm_HandSolder
C20, C21: 27pF; C_0603_1608Metric_Pad1.08x0.95mm_HandSolder
C22: 470pF; C_0603_1608Metric_Pad1.08x0.95mm_HandSolder
C24, C26, C28, C36, C38: 10nF; C_0603_1608Metric_Pad1.08x0.95mm_HandSolder
C30: 4.7uF; C_0603_1608Metric_Pad1.08x0.95mm_HandSolder
C31, C32, C33, C34: 10pF DNP; C_0603_1608Metric_Pad1.08x0.95mm_HandSolder
C35: 22nF; C_0603_1608Metric_Pad1.08x0.95mm_HandSolder
C39, C40, C41, C42: 10uF; C_0603_1608Metric_Pad1.08x0.95mm_HandSolder
D1, D2, D3, D4: D_Small; D_SMA-SMB_Universal_Handsoldering
D5: LED_Small; LED_0603_1608Metric_Pad1.05x0.95mm_HandSolder
FB1: FerriteBead_Small; C_0603_1608Metric_Pad1.08x0.95mm_HandSolder
J1: RJ45_Amphenol_RJMG1BD3B8K1ANR
J2, J3, J4, J5, J11: Conn_01x02_Female; JST_PH_S2B-PH-SM4-TB_1x02-1MP_P2.00mm_Horizontal
J6, J7, J8, J9, J10, J15: Conn_01x03_Female; JST_PH_S3B-PH-SM4-TB_1x03-1MP_P2.00mm_Horizontal
J12: Conn_01x01; PinHeader_1x01_P2.54mm_Vertical
J13: Conn_01x03_Male; JST_VH_B3P-VH-B_1x03_P3.96mm_Vertical
J14: Conn_01x05_Female; JST_PH_B5B-PH-K_1x05_P2.00mm_Vertical
R1, R2, R3, R4, R5, R8, R9, R10, R16, R18: 10K; R_0603_1608Metric_Pad0.98x0.95mm_HandSolder
R6, R7: 150; R_0603_1608Metric_Pad0.98x0.95mm_HandSolder
R11, R12, R13, R22: 33; R_0603_1608Metric_Pad0.98x0.95mm_HandSolder
R14, R17, R19, R23, R27, R28: 1.5K; R_0603_1608Metric_Pad0.98x0.95mm_HandSolder
R15: 12.1K; R_0603_1608Metric_Pad0.98x0.95mm_HandSolder
R20, R21, R25, R30, R31: 750; R_0603_1608Metric_Pad0.98x0.95mm_HandSolder
R24, R26, R29, R32: 49.9 1%; R_0603_1608Metric_Pad0.98x0.95mm_HandSolder
R33: 1K; R_0603_1608Metric_Pad0.98x0.95mm_HandSolder
R34: 1M; R_0603_1608Metric_Pad0.98x0.95mm_HandSolder
R35: 350; R_0603_1608Metric_Pad0.98x0.95mm_HandSolder
R36: 220; R_0603_1608Metric_Pad0.98x0.95mm_HandSolder
SW1: SW_RST; SW_SPST_PTS810
U1: STM32F407ZETx; LQFP-144_20x20mm_P0.5mm
U2, U3, U7, U8: MCP1416; SOT-23-5
U4, U5, U9, U10: IPD60R600; TO-252-3_TabPin2-HandSolder
U6: LAN8742; VQFN-24-1EP_4x4mm_P0.5mm_EP2.45x2.45mm
U11: TL431DBZ; SOT-23
U12: AD8495; MSOP-8_3x3mm_P0.65mm
U13: TLP250; DIP-8_W7.62mm
U14: NCP1117-5.0_TO252; TO-252-2-HandSolder
U15: NCP1117-3.3_TO252; TO-252-2-HandSolder
Y1, Y2: 25 MHz; Crystal_SMD_HC49-SD_HandSoldering

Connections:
+5V: C41.1, J7.1, J8.1, J9.1, J10.1, J15.1, U14.2 (VO)
+12V: C39.1, C40.1, FB1.1, U2.2 (Vdd), U3.2 (Vdd), U7.2 (Vdd), U8.2 (Vdd), U14.3 (VI), U15.3 (VI)
/RX+: C34.1, J1.R3 (RD+), R32.2, U6.23 (RXP)
/RX-: C33.1, J1.R6 (RD-), R29.2, U6.22 (RXN)
/TX+: C32.1, J1.R1 (TD+), R26.2, U6.21 (TXP)
/TX-: C31.1, J1.R2 (TD-), R24.2, U6.20 (TXN)
ADC1_IN3: R17.1, R20.1, U1.37 (PA3)
ADC1_IN4: R27.1, R30.1, U1.40 (PA4)
ADC2_IN5: R19.1, R21.1, U1.41 (PA5)
ADC2_IN6: R28.1, R31.1, U1.42 (PA6)
ADC3_IN7: U1.21 (PF9), U12.5 (SENSE), U12.6
ADC3_IN8: R23.1, R25.1, U1.22 (PF10)
ETH_CRS_DV: R5.1, R13.1, U1.43 (PA7)
ETH_LED1: J1.L4 (LEDG_A), R7.1
ETH_LED2: J1.L1 (LEDY_A), R6.1
ETH_MDC: U1.27 (PC1), U6.13 (MDC)
ETH_MDIO: R14.2, U1.36 (PA2), U6.12 (MDIO)
ETH_REF_CLK: R22.2, U1.35 (PA1)
ETH_RXD0: R12.2, U1.44 (PC4)
ETH_RXD1: R11.1, U1.45 (PC5)
ETH_TXD0: U1.73 (PB12), U6.17 (TDX0)
ETH_TXD1: U1.74 (PB13), U6.18 (TXD1)
ETH_TX_EN: U1.70 (PB11), U6.16 (TXEN)
Earth: J1.13 (SHIELD), J1.R8 (GND), J12.1
GND: C1.1, C2.1, C3.1, C4.1, C5.2, C6.2, C7.2, C8.2, C9.2, C10.2, C11.2, C12.2, C13.2, C14.2, C15.2, C16.2, C17.2, C18.1, C19.2, C20.1, C21.1, C22.1, C23.2, C24.2, C25.2, C26.2, C27.2, C28.2, C29.2, C30.2, C31.2, C32.2, C33.2, C34.2, C35.1, C36.1, C38.2, C39.2, C40.2, C41.2, C42.2, J1.L2 (LEDY_K), J1.L3 (LEDG_K), J7.3, J8.3, J9.3, J10.3, J13.3, J14.5, J15.3, R1.1, R8.1, R9.2, R10.2, R15.2, R17.2, R19.2, R23.2, R27.2, R28.2, R34.2, R36.2, SW1.2 (B), U1.16 (VSS), U1.31 (VSSA), U1.38 (VSS), U1.51 (VSS), U1.61 (VSS), U1.83 (VSS), U1.94 (VSS), U1.107 (VSS), U1.120 (VSS), U1.130 (VSS), U2.4 (GND), U3.4 (GND), U4.3 (SOURCE), U5.3 (SOURCE), U6.25 (VSS), U7.4 (GND), U8.4 (GND), U9.3 (SOURCE), U10.3 (SOURCE), U11.3 (A), U12.3 (-Vs), U13.3 (C), U14.1 (GND), U15.1 (GND)
unnamed: C1.2, U1.106 (VCAP_2)
unnamed: C2.2, U1.23 (PH0), Y1.2
unnamed: C3.2, U1.24 (PH1), Y1.1
unnamed: C4.2, U1.71 (VCAP_1)
unnamed: C18.2, C22.2, U6.6 (VDDCR)
unnamed: C20.2, U6.4 (XTAL2), Y2.2
unnamed: C21.2, U6.5 (XTAl1), Y2.1
unnamed: D5.1 (K), R36.1
unnamed: D5.2 (A), U1.4 (PE5)
unnamed: FB1.2, J13.2
unnamed: R1.2, U1.138 (BOOT0)
unnamed: R6.2, R9.1, U6.2 (LED2)
unnamed: R8.2, U6.10 (RXER)
unnamed: R7.2, R10.1, U6.3 (LED1)
unnamed: R3.1, R11.2, U6.7 (RXD1)
unnamed: R4.1, R12.1, U6.8 (RXD0)
unnamed: R13.2, U6.11 (CRS_DV)
unnamed: R15.1, U6.24 (RBIAS)
unnamed: R16.1, U6.15 (~RST)
unnamed: R18.1, R22.1, U6.14 (~INT)
unnamed: R33.1, U11.1 (K), U11.2 (REF), U12.2 (REF)
unnamed: R35.2, U13.2 (A)
unnamed: U2.5 (OUT), U4.1 (GATE)
unnamed: U3.5 (OUT), U5.1 (GATE)
unnamed: U7.5 (OUT), U9.1 (GATE)
unnamed: U8.5 (OUT), U10.1 (GATE)
PS1: J7.2, R20.2
PS2: J8.2, R30.2
PS3: J9.2, R21.2
PS4: J10.2, R31.2
PS5: J15.2, R25.2
RST: C17.1, J14.1, R2.2, SW1.1 (A), U1.25 (NRST)
SPARK: J6.2, U13.6 (VO)
SPARK_CTRL: R35.1, U1.60 (PE9)
SPARK_GND: J6.3, U13.5 (VEE)
SPARK_VCC: J6.1, U13.8 (VCC)
SV1: D1.2 (A), J2.1, U4.2 (DRAIN)
SV1_CTRL: U1.104 (PA12), U2.3 (IN)
SV2: D2.2 (A), J3.1, U5.2 (DRAIN)
SV2_CTRL: U1.103 (PA11), U3.3 (IN)
SV3: D3.2 (A), J4.1, U9.2 (DRAIN)
SV3_CTRL: U1.102 (PA10), U7.3 (IN)
SV4: D4.2 (A), J5.1, U10.2 (DRAIN)
SV4_CTRL: U1.101 (PA9), U8.3 (IN)
SWCLK: J14.2, U1.109 (PA14)
SWDIO: J14.3, U1.105 (PA13)
TS1+: C36.2, C37.1, J11.1, U12.8 (+IN)
TS1-: C37.2, C38.1, J11.2, R34.1, U12.1 (-IN)
VBAT: C5.1, C6.1, C7.1, C8.1, C9.1, C10.1, C11.1, C12.1, C13.1, C14.1, C15.1, C16.1, C19.1, C23.1, C24.1, C25.1, C26.1, C27.1, C28.1, C29.1, C30.1, C35.2, C42.1, J1.R4 (TCT), J1.R5 (RCT), R2.1, R3.2, R4.2, R5.2, R14.1, R16.2, R18.2, R24.1, R26.1, R29.1, R32.1, R33.2, U1.6 (VBAT), U1.17 (VDD), U1.30 (VDD), U1.32 (VREF+), U1.33 (VDDA), U1.39 (VDD), U1.52 (VDD), U1.62 (VDD), U1.72 (VDD), U1.84 (VDD), U1.95 (VDD), U1.108 (VDD), U1.121 (VDD), U1.131 (VDD), U1.143 (PDR_ON), U1.144 (VDD), U6.1 (VDD2A), U6.9 (VDDIO), U6.19 (VDD1A), U12.7 (+Vs), U15.2 (VO)
Vdrive: D1.1 (K), D2.1 (K), D3.1 (K), D4.1 (K), J2.2, J3.2, J4.2, J5.2, J13.1
